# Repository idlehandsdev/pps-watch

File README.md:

# PPS Watch  

### The Most Accurate Watch that Doesn't Tell Time.

---

## What it does

- Receives GPS , achieves position/time fix
- Outputs 1PPS (one pulse per second) on the GPS module's hardware TIMEPULSE pin, silent until locked, active at 1Hz once locked
- Distributes that PPS signal across a BNC connector via buffered outputs
- Accepts an external PPS reference, compares it against the GPS PPS via a hardware XOR phase comparator, with LED indicators for PPS presence and phase offset
- No microcontroller. No firmware. The GPS module's hardware PPS pin drives the LEDs and BNC outputs directly through logic buffers.

## Hardware

- **GPS module:** u-blox MAX-M10S
- **Antenna:** External via SMA, no onboard antenna. Direct-mount stub antennas (Quectel YEGT001AA right-angle / YEGT002AA straight) screw directly onto the SMA connector, no cable
- **Buffering:** 2x 74HC125 quad buffer (GPS output side, external input side)
- **Comparator:** 74AHC1G86 single XOR gate
- **Indicators:** 0805 SMD LEDs -- 1x red (PPS), 2x green (fix / external PPS)
- **Power:** CR2450 coin cell, switched via SW1, V_BCKP always connected
- **Config port:** Qwiic (I2C) for one-time setup via u-center if needed
- **Connectors:** 2x BNC, 1x SMA (antenna), 1x Qwiic

See the schematic for full signal flow and the BOM for part numbers.

## CAD

This is a KiCad project. PCB mechanical design and 3D assembly were done in Fusion 360.

**Fusion 360 share link:** https://a360.co/4xXmWnG

## BOM

- ** BOM should be up to date! - https://www.digikey.ca/en/mylists/list/XIH163JVIJ
- ** R2 was a 0R resistor, but the BOM now includes a PTC instead.

| Reference | Qty | Value | Digikey Part No. |
|---|---|---|---|
| AE3 | 1 | YEGT002AA | [2958-YEGT002AA-ND](https://www.digikey.com/en/products/detail/quectel/YEGT002AA/17101891) |
| BT2 | 1 | BU2450SM-JJ-G | [BU2450SM-JJ-GCT-ND](https://www.digikey.com/en/products/detail/mpd-memory-protection-devices/BU2450SM-JJ-GTR/3028728) |
| C1 | 1 | 100pF C0G | 311-1111-1-ND |
| C2, C3, C4, C5 | 4 | 0.1uF | 311-4348-1-ND |
| D1 | 1 | LED Red 0805 | 160-1415-1-ND |
| D2 | 1 | PESD0402-140 | [PESD0402-140CT-ND](https://www.digikey.com/en/products/detail/littelfuse-inc/PESD0402-140/1968526) |
| D3, D4 | 2 | LED Green 0805 | [475-LGR971-KN-1TR-ND](https://www.digikey.com/en/products/detail/LG%20R971-KN-1/475-1410-1-ND/1802598) |
| J1, J4 | 2 | BNC 2466267-1 | 17-2466267-1-ND |
| J2 | 1 | CONSMA002-SMD-G-T | 343-CONSMA002-SMD-G-TCT-ND |
| J6 | 1 | Qwiic | 1568-14417-ND |
| L1 | 1 | Ferrite Bead | 490-1040-1-ND |
| R1 | 1 | 470R | 311-470ARCT-ND |
| R2 | 1 | 500mA PolyFuse | F2772CT-ND |
| R3, R6 | 2 | 10K | 311-10KARCT-ND |
| R4, R5 | 2 | 330R | 311-330ARCT-ND |
| SW1 | 1 | Power Switch SPDT | 401-2016-1-ND |
| U1 | 1 | MAX-M10S | 672-MAX-M10S-00BTR-ND |
| U3, U6 | 2 | 74HC125D | [74HC125DCT-ND](https://www.digikey.com/en/products/detail/toshiba-semiconductor-and-storage/74HC125D/6198795) |
| U5 | 1 | 74AHC1G86 | [296-1094-1-ND](https://www.digikey.com/en/products/detail/texas-instruments/SN74AHC1G86DBVR/276738) |

## Watch Assembly

### 3D Printed Parts

Print the following files from the `CAD/` folder:

- `CAD/pcb_frame_mount.stl` -- frame that holds the PCB
- `CAD/watch_band_mount.stl` -- mounts the band to the frame

### Watch Band

Any standard 22mm watch band works. Tested with:

[Bandini Nylon Sports Watch Band Strap 22mm](https://www.amazon.com/dp/B09R2BVRWQ)

### Hardware

- 2 x M2x6mm Flat Head Plastic Threading Screws to mount body to strap mount. - https://www.mcmaster.com/90485A415/
- 2 x M3x6mm Pan Head Plastic Threading Screws for mounting PCB to Body - https://www.mcmaster.com/99461A939/
- 2 x M3x35mm Round Head Machine Screws to mount strap. Just Thread into the plastic snugly https://www.mcmaster.com/92000A134/
---

*Felix Corp -- Idle Hands Dev R&D Division*
*Asset Tag: FC-IDH-UTC-001*

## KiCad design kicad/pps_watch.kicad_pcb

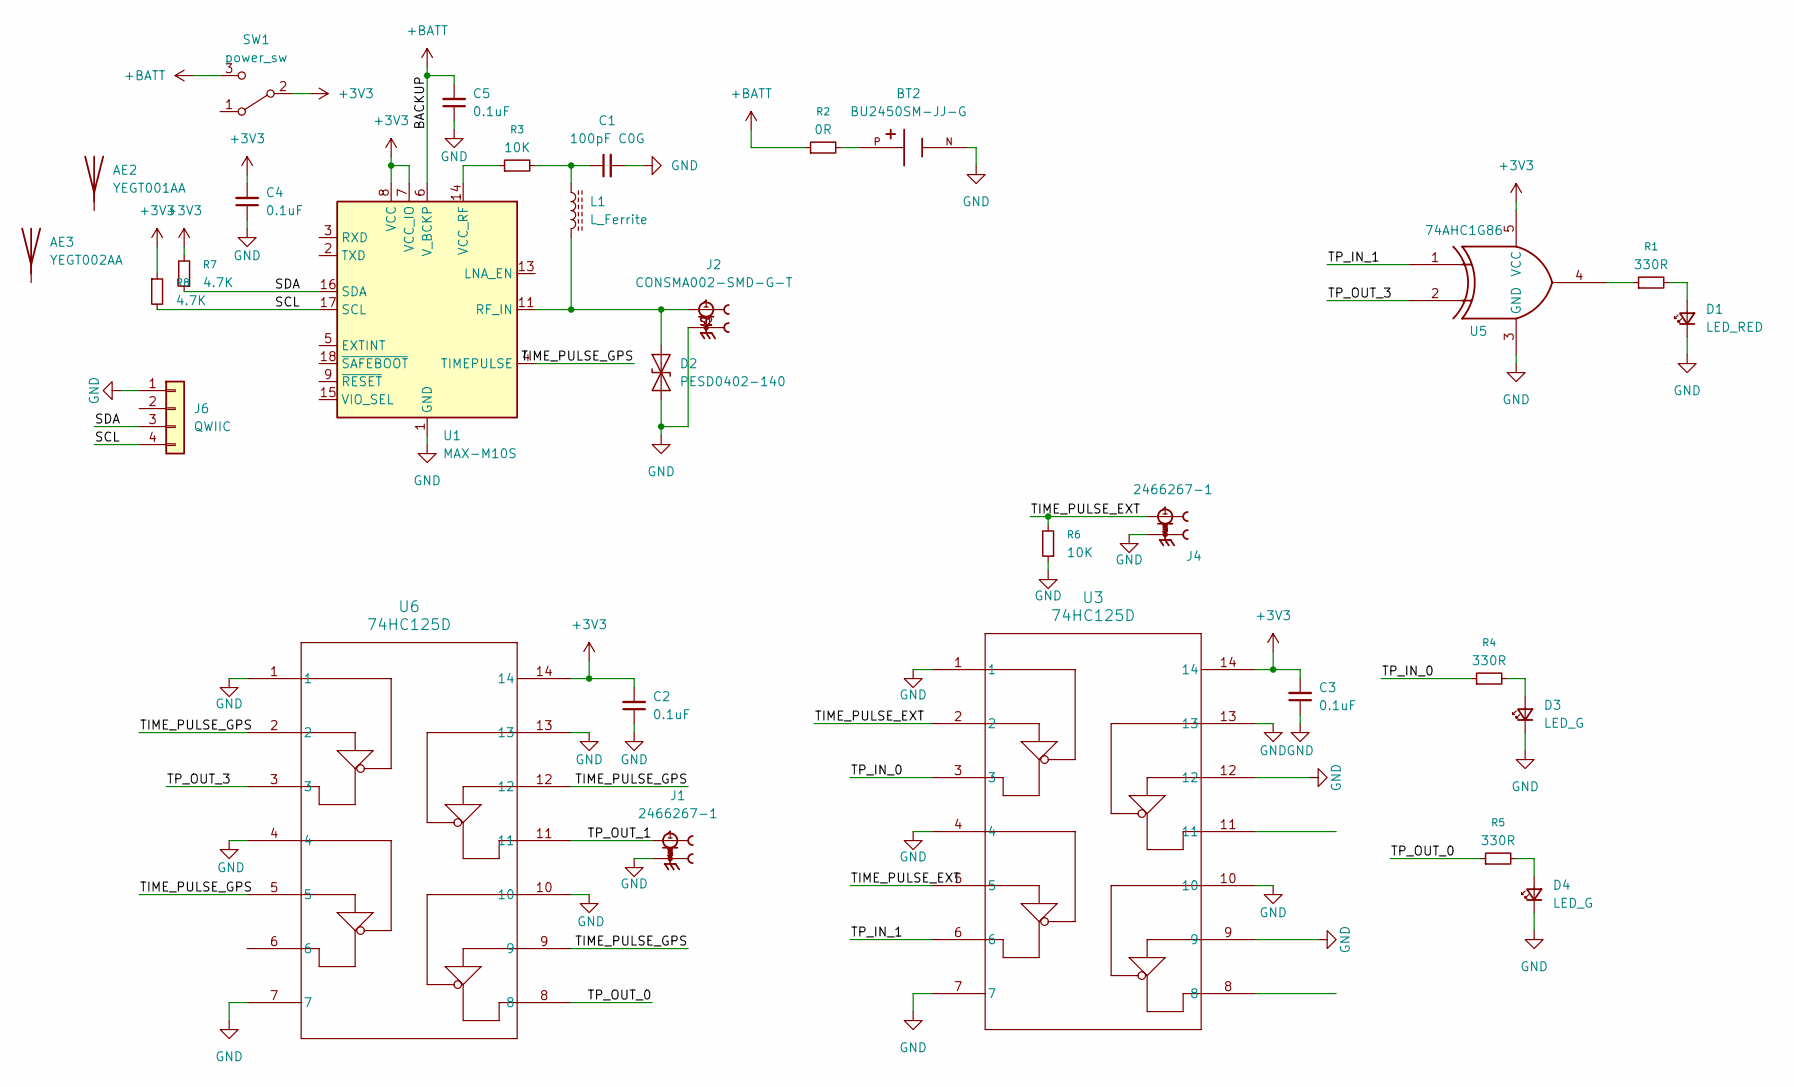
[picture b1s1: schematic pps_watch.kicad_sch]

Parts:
AE2: YEGT001AA; Digikey Part No. 2958-YEGT001AA-ND
AE3: YEGT002AA; Digikey Part No. 2958-YEGT002AA-ND
BT2: BU2450SM-JJ-G; BAT_BU2450SM-JJ-G; PARTREV J; Digikey Part No. BU2450SM-JJ-GCT-ND
C1: 100pF C0G; C_0805_2012Metric; Digikey Part No. 311-1111-1-ND
C2, C3, C4, C5: 0.1uF; C_0805_2012Metric
D1: LED_RED; LED_0805_2012Metric; Digikey Part No. 160-1415-1-ND
D2: PESD0402-140; D_SOD-923; Digikey Part No. PESD0402-140CT-ND
D3, D4: LED_G; LED_0805_2012Metric; Digikey Part No. 475-LGR971-KN-1TR-ND
J1, J4: 2466267-1; TE_2466267-1; PARTREV A1; Digikey Part No. 17-2466267-1-ND
J2: CONSMA002-SMD-G-T; LINX_CONSMA002-SMD-G-T; Digikey Part No. 343-CONSMA002-SMD-G-TCT-ND
J6: QWIIC; CONN_SM04B-SRSS-TB_JST; Digikey Part No. 1528-4328-ND
L1: L_Ferrite; L_0805_2012Metric; Digikey Part No. 490-1040-1-ND
R1, R4, R5: 330R; R_0805_2012Metric
R2: 0R; R_0805_2012Metric
R3, R6: 10K; R_0805_2012Metric
R7, R8: 4.7K; R_0805_2012Metric
SW1: power_sw; SW_SPDT_PCM12; Digikey Part No. 401-2016-1-ND
U1: MAX-M10S; ublox_MAX; Digikey Part No. 672-MAX-M10S-00BTR-ND
U3, U6: 74HC125D; SOIC14_TOS; Digikey Part No. 74HC125DCT-ND
U5: 74AHC1G86; SOT-23-5; Digikey Part No. 296-1094-1-ND

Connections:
+3V3: C2.2, C3.2, C4.2, R7.2, R8.1, SW1.2 (B), U1.7 (VCC_IO), U1.8 (VCC), U3.14, U5.5 (VCC), U6.14
+BATT: C5.2, R2.1, SW1.3 (C), U1.6 (V_BCKP)
/SCL: J6.4, R8.2, U1.17 (SCL)
/SDA: J6.3, R7.1, U1.16 (SDA)
/TIME_PULSE_EXT: J4.1, R6.2, U3.2, U3.5
/TIME_PULSE_GPS: U1.4 (TIMEPULSE), U6.2, U6.5, U6.9, U6.12
/TP_IN_0: R4.1, U3.3
/TP_IN_1: U3.6, U5.1
/TP_OUT_0: R5.1, U6.8
/TP_OUT_1: J1.1, U6.11
/TP_OUT_3: U5.2, U6.3
GND: BT2.N, C1.2, C2.1, C3.1, C4.1, C5.1, D1.1 (K), D2.1 (A1), D3.1 (K), D4.1 (K), J1.2, J1.3, J1.4, J1.5, J2.S1, J2.S2, J4.2, J4.3, J4.4, J4.5, J6.1, R6.1, U1.1 (GND), U1.10 (GND), U1.12 (GND), U3.1, U3.4, U3.7, U3.9, U3.10, U3.12, U3.13, U5.3 (GND), U6.1, U6.4, U6.7, U6.10, U6.13
unnamed: BT2.P, R2.2
unnamed: C1.1, L1.1, R3.2
unnamed: D1.2 (A), R1.2
unnamed: D2.2 (A2), J2.1, L1.2, U1.11 (RF_IN)
unnamed: D3.2 (A), R4.2
unnamed: D4.2 (A), R5.2
unnamed: R1.1, U5.4
unnamed: R3.1, U1.14 (VCC_RF)

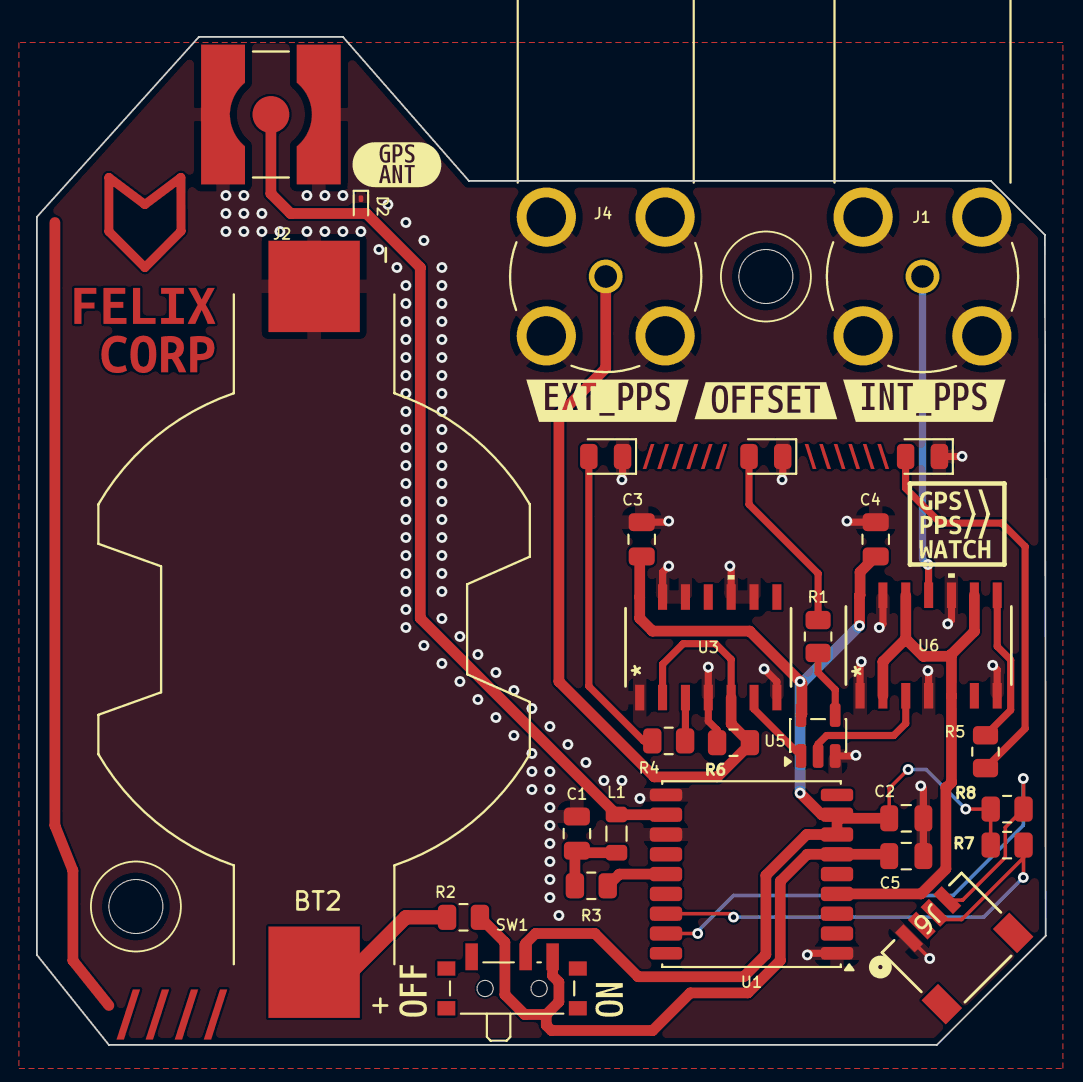
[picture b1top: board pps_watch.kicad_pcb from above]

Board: 2 copper layers, 56.0 x 56.0 mm, 39 parts (0 on the bottom side), 20 nets.

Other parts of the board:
kibuzzard-6A225EFE: G***; kibuzzard-6A225EFE
kibuzzard-6A2251CD: G***; kibuzzard-6A2251CD
kibuzzard-6A2254F6: G***; kibuzzard-6A2254F6
kibuzzard-6A2255A9: G***; kibuzzard-6A2255A9
kibuzzard-6A2263B9: G***; kibuzzard-6A2263B9
kibuzzard-6A22543C: G***; kibuzzard-6A22543C
kibuzzard-6A225147: G***; kibuzzard-6A225147
kibuzzard-6A225388: G***; kibuzzard-6A225388
kibuzzard-6A225392: G***; kibuzzard-6A225392
kibuzzard-6A226669: G***; kibuzzard-6A226669
kibuzzard-6A226675: G***; kibuzzard-6A226675
